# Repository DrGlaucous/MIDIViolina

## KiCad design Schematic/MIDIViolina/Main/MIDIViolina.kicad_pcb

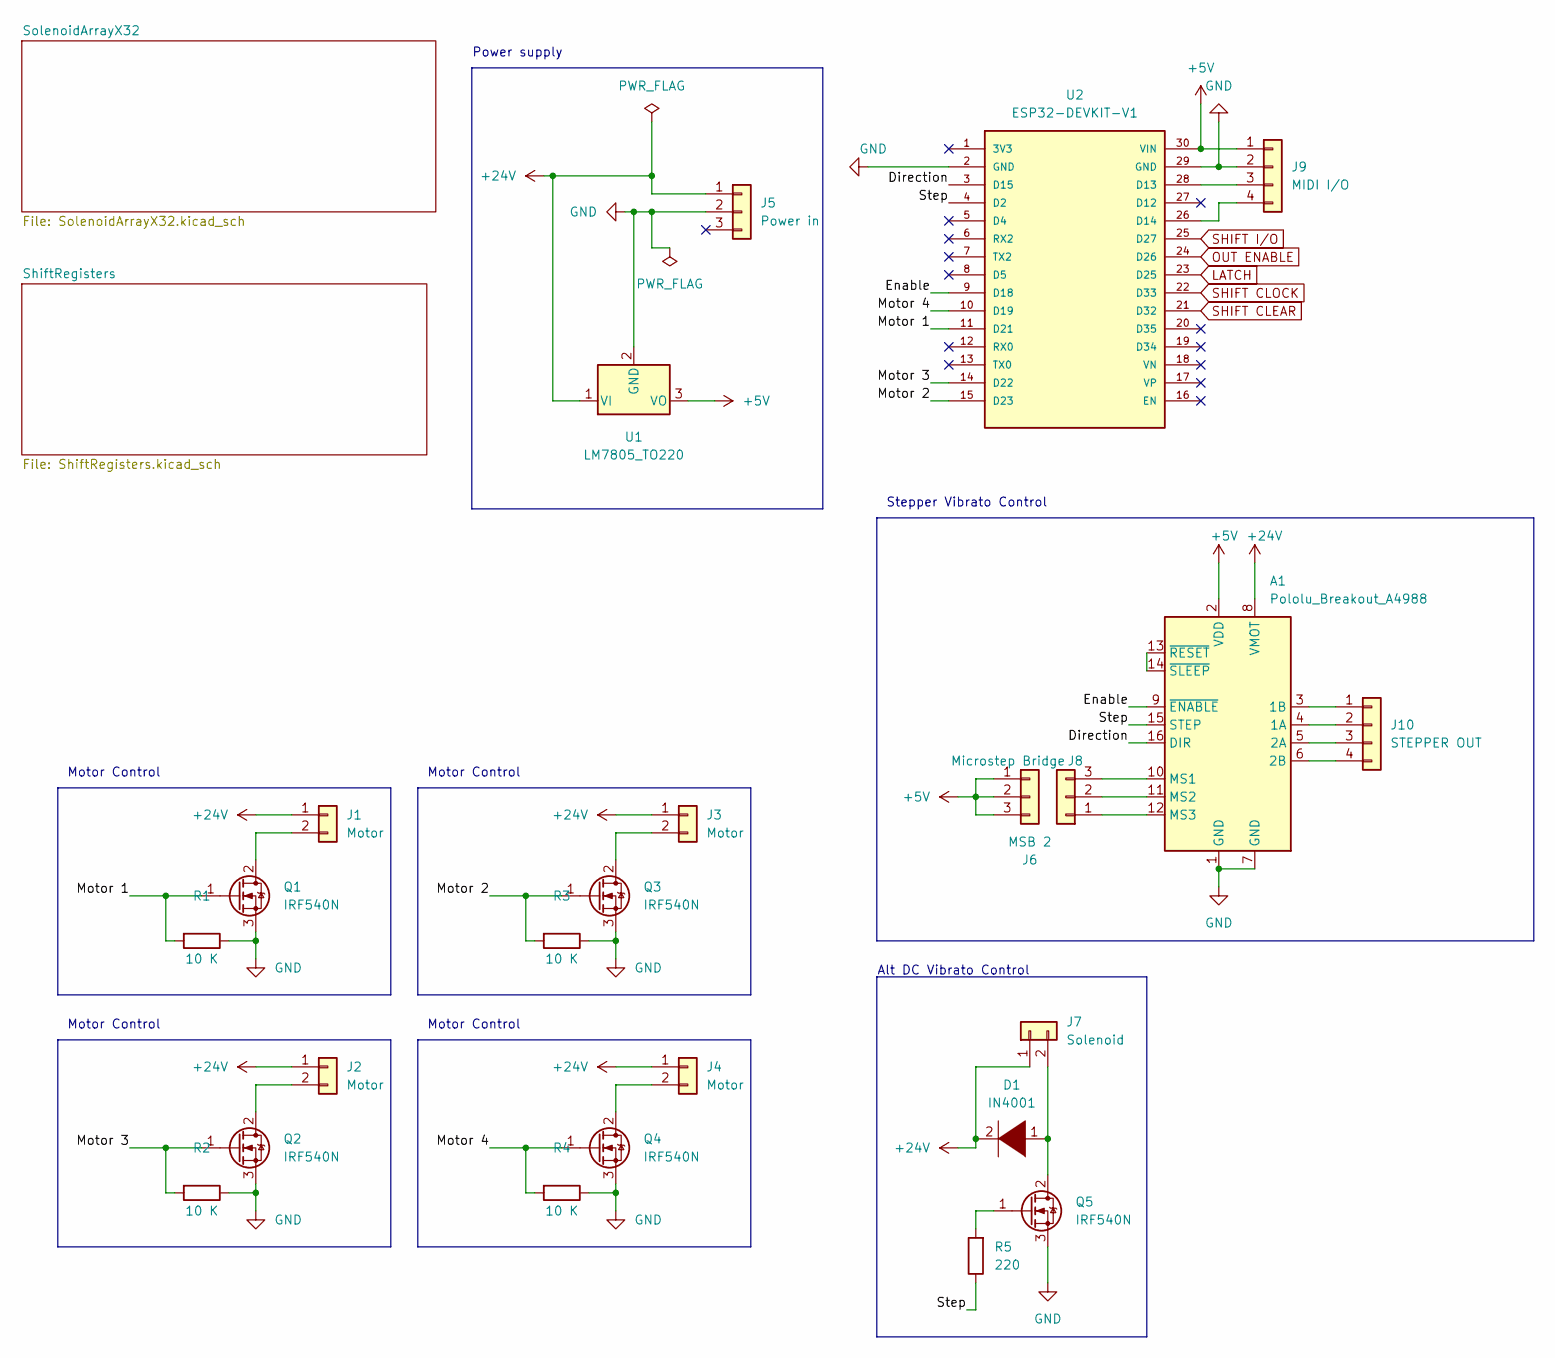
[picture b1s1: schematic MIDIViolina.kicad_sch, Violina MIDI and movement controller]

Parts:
A1: Pololu_Breakout_A4988; Pololu_Breakout-16_15.2x20.3mm
D1: IN4001; D_DO-41_SOD81_P7.62mm_Horizontal
J1, J2, J3, J4: Motor; PinHeader_1x02_P2.54mm_Vertical
J5: Power in; PinHeader_1x03_P2.54mm_Vertical
J6: MSB 2; PinHeader_1x03_P2.54mm_Vertical
J7: Solenoid; PinHeader_1x02_P2.54mm_Vertical
J8: Microstep Bridge; PinHeader_1x03_P2.54mm_Vertical
J9: MIDI I/O; PinHeader_1x04_P2.54mm_Vertical
J10: STEPPER OUT; PinHeader_1x04_P2.54mm_Vertical
Q1, Q2, Q3, Q4, Q5: IRF540N; TO-220-3_Vertical
R1, R2, R3, R4: 10 K; R_Axial_DIN0207_L6.3mm_D2.5mm_P7.62mm_Horizontal
R5: 220; R_Axial_DIN0207_L6.3mm_D2.5mm_P7.62mm_Horizontal
U1: LM7805_TO220; TO-220-3_Vertical
U2: ESP32-DEVKIT-V1; MODULE_ESP32_DEVKIT_V1; PARTREV N/A

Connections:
+5V: A1.2 (VDD), J6.1, J6.2, J6.3, J9.1, U1.3 (VO), U2.30 (VIN); also elsewhere on the board
+24V: A1.8 (VMOT), D1.2 (A), J1.1, J2.1, J3.1, J4.1, J5.1, J7.1, U1.1 (VI); also elsewhere on the board
/Direction: A1.16 (DIR), U2.3 (D15)
/Enable: A1.9 (~ENABLE), U2.9 (D18)
/Motor 1: Q1.1 (G), R1.2, U2.11 (D21)
/Motor 2: Q3.1 (G), R3.2, U2.15 (D23)
/Motor 3: Q2.1 (G), R2.2, U2.14 (D22)
/Motor 4: Q4.1 (G), R4.2, U2.10 (D19)
/Step: A1.15 (STEP), R5.1, U2.4 (D2)
GND: A1.1 (GND), A1.7 (GND), J5.2, J9.2, Q1.3 (S), Q2.3 (S), Q3.3 (S), Q4.3 (S), Q5.3 (S), R1.1, R2.1, R3.1, R4.1, U1.2 (GND), U2.2 (GND), U2.29 (GND); also elsewhere on the board
LATCH: U2.23 (D25); also elsewhere on the board
unnamed: A1.3 (1B), J10.1
unnamed: A1.4 (1A), J10.2
unnamed: A1.5 (2A), J10.3
unnamed: A1.6 (2B), J10.4
unnamed: A1.10 (MS1), J8.3
unnamed: A1.11 (MS2), J8.2
unnamed: A1.12 (MS3), J8.1
unnamed: A1.13 (~RESET), A1.14 (~SLEEP)
unnamed: D1.1 (K), J7.2, Q5.2 (D)
unnamed: J1.2, Q1.2 (D)
unnamed: J2.2, Q2.2 (D)
unnamed: J3.2, Q3.2 (D)
unnamed: J4.2, Q4.2 (D)
unnamed: J9.3, U2.28 (D13)
unnamed: J9.4, U2.26 (D14)
unnamed: Q5.1 (G), R5.2
OUT ENABLE: U2.24 (D26); also elsewhere on the board
SHIFT CLEAR: U2.21 (D32); also elsewhere on the board
SHIFT CLOCK: U2.22 (D33); also elsewhere on the board
SHIFT I/O: U2.25 (D27); also elsewhere on the board

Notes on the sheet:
Motor Control
Alt DC Vibrato Control
Stepper Vibrato Control
Power supply

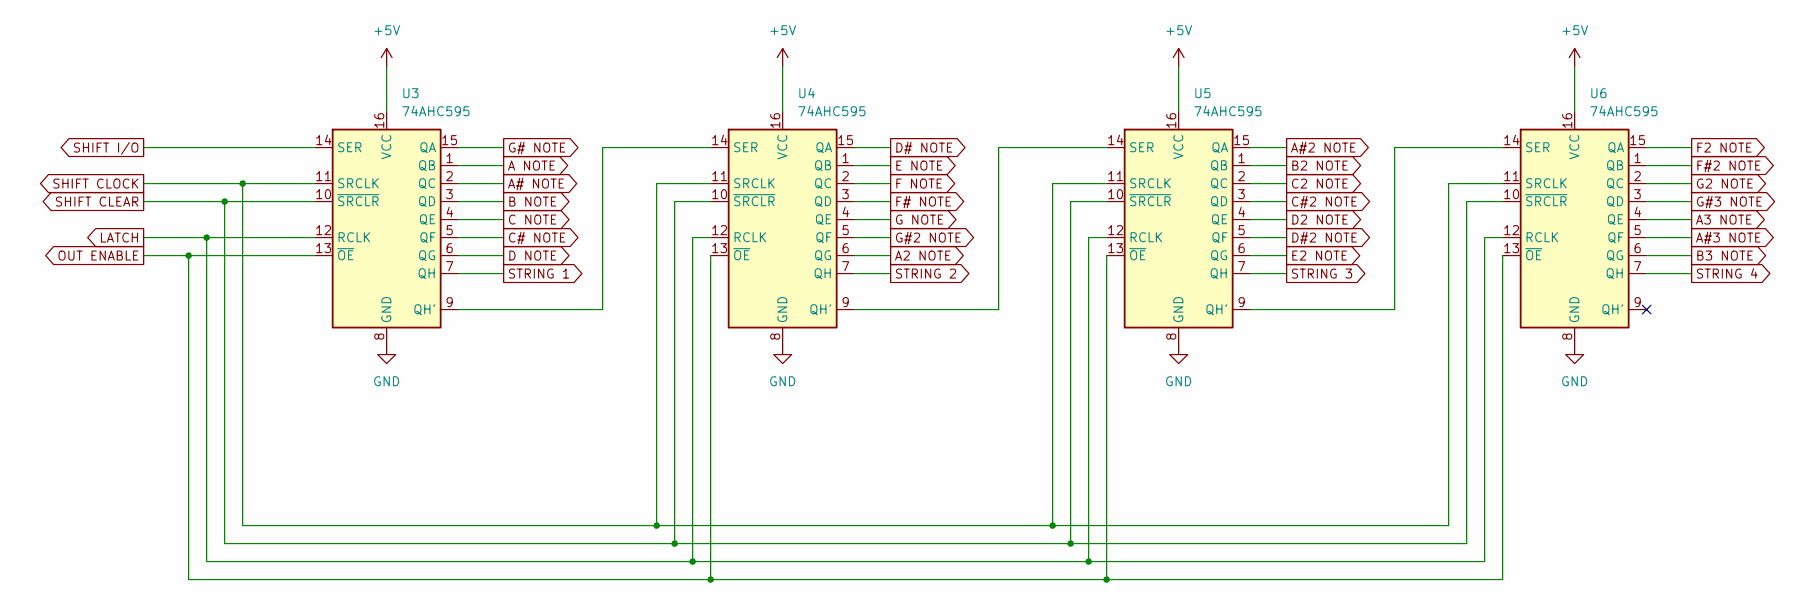
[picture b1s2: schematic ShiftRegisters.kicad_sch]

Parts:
U3, U4, U5, U6: 74AHC595; DIP-16_W7.62mm_LongPads

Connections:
+5V: U3.16 (VCC), U4.16 (VCC), U5.16 (VCC), U6.16 (VCC); also elsewhere on the board
A2 NOTE: U4.6 (QG); also elsewhere on the board
A3 NOTE: U6.4 (QE); also elsewhere on the board
A NOTE: U3.1 (QB); also elsewhere on the board
A#2 NOTE: U5.15 (QA); also elsewhere on the board
A#3 NOTE: U6.5 (QF); also elsewhere on the board
A# NOTE: U3.2 (QC); also elsewhere on the board
B2 NOTE: U5.1 (QB); also elsewhere on the board
B3 NOTE: U6.6 (QG); also elsewhere on the board
B NOTE: U3.3 (QD); also elsewhere on the board
C2 NOTE: U5.2 (QC); also elsewhere on the board
C NOTE: U3.4 (QE); also elsewhere on the board
C#2 NOTE: U5.3 (QD); also elsewhere on the board
C# NOTE: U3.5 (QF); also elsewhere on the board
D2 NOTE: U5.4 (QE); also elsewhere on the board
D NOTE: U3.6 (QG); also elsewhere on the board
D#2 NOTE: U5.5 (QF); also elsewhere on the board
D# NOTE: U4.15 (QA); also elsewhere on the board
E2 NOTE: U5.6 (QG); also elsewhere on the board
E NOTE: U4.1 (QB); also elsewhere on the board
F2 NOTE: U6.15 (QA); also elsewhere on the board
F NOTE: U4.2 (QC); also elsewhere on the board
F#2 NOTE: U6.1 (QB); also elsewhere on the board
F# NOTE: U4.3 (QD); also elsewhere on the board
G2 NOTE: U6.2 (QC); also elsewhere on the board
G NOTE: U4.4 (QE); also elsewhere on the board
G#2 NOTE: U4.5 (QF); also elsewhere on the board
G#3 NOTE: U6.3 (QD); also elsewhere on the board
G# NOTE: U3.15 (QA); also elsewhere on the board
GND: U3.8 (GND), U4.8 (GND), U5.8 (GND), U6.8 (GND); also elsewhere on the board
LATCH: U3.12 (RCLK), U4.12 (RCLK), U5.12 (RCLK), U6.12 (RCLK); also elsewhere on the board
unnamed: U3.9 (QH'), U4.14 (SER)
unnamed: U4.9 (QH'), U5.14 (SER)
unnamed: U5.9 (QH'), U6.14 (SER)
OUT ENABLE: U3.13 (~OE), U4.13 (~OE), U5.13 (~OE), U6.13 (~OE); also elsewhere on the board
SHIFT CLEAR: U3.10 (~SRCLR), U4.10 (~SRCLR), U5.10 (~SRCLR), U6.10 (~SRCLR); also elsewhere on the board
SHIFT CLOCK: U3.11 (SRCLK), U4.11 (SRCLK), U5.11 (SRCLK), U6.11 (SRCLK); also elsewhere on the board
SHIFT I/O: U3.14 (SER); also elsewhere on the board
STRING 1: U3.7 (QH); also elsewhere on the board
STRING 2: U4.7 (QH); also elsewhere on the board
STRING 3: U5.7 (QH); also elsewhere on the board
STRING 4: U6.7 (QH); also elsewhere on the board

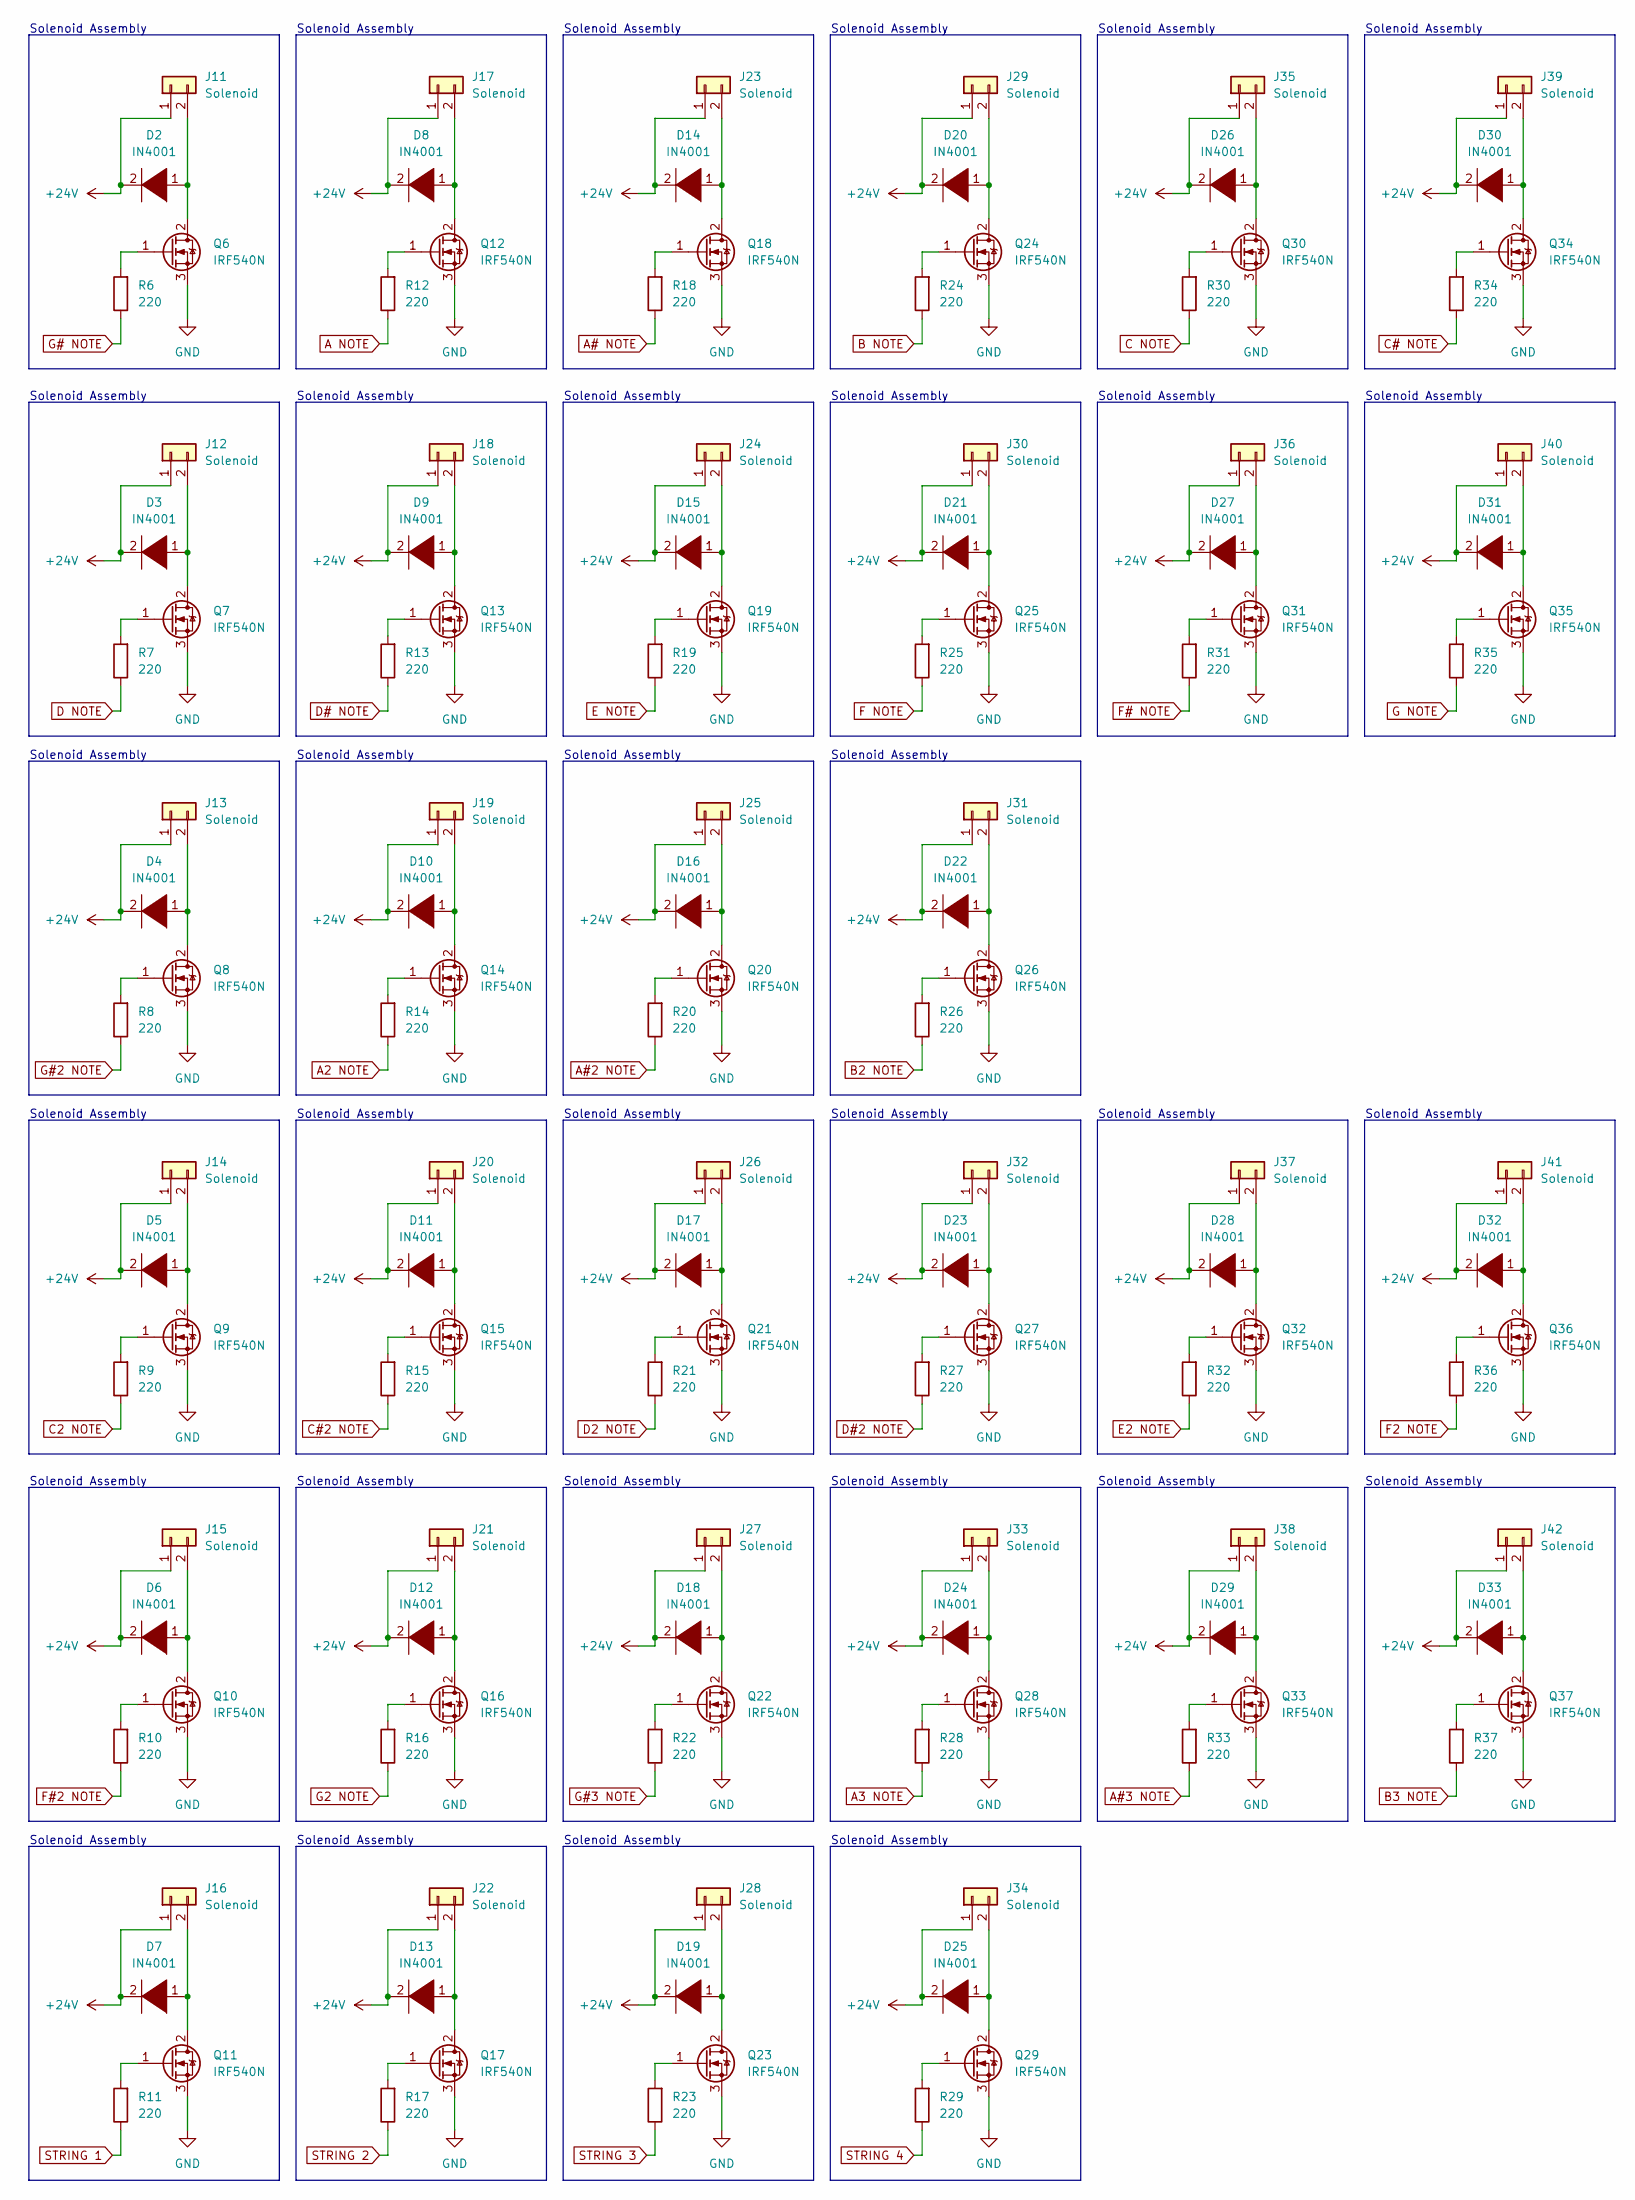
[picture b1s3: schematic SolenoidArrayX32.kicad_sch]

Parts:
D2, D3, D4, D5, D6, D7, D8, D9, D10, D11, D12, D13, D14, D15, D16, D17, D18, D19, D20, D21, D22, D23, D24, D25, D26, D27, D28, D29, D30, D31, D32, D33: IN4001; D_DO-41_SOD81_P7.62mm_Horizontal
J11, J12, J13, J14, J15, J16, J17, J18, J19, J20, J21, J22, J23, J24, J25, J26, J27, J28, J29, J30, J31, J32, J33, J34, J35, J36, J37, J38, J39, J40, J41, J42: Solenoid; PinHeader_1x02_P2.54mm_Vertical
Q6, Q7, Q8, Q9, Q10, Q11, Q12, Q13, Q14, Q15, Q16, Q17, Q18, Q19, Q20, Q21, Q22, Q23, Q24, Q25, Q26, Q27, Q28, Q29, Q30, Q31, Q32, Q33, Q34, Q35, Q36, Q37: IRF540N; TO-220-3_Vertical
R6, R7, R8, R9, R10, R11, R12, R13, R14, R15, R16, R17, R18, R19, R20, R21, R22, R23, R24, R25, R26, R27, R28, R29, R30, R31, R32, R33, R34, R35, R36, R37: 220; R_Axial_DIN0207_L6.3mm_D2.5mm_P7.62mm_Horizontal

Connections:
+24V: D2.2 (A), D3.2 (A), D4.2 (A), D5.2 (A), D6.2 (A), D7.2 (A), D8.2 (A), D9.2 (A), D10.2 (A), D11.2 (A), D12.2 (A), D13.2 (A), D14.2 (A), D15.2 (A), D16.2 (A), D17.2 (A), D18.2 (A), D19.2 (A), D20.2 (A), D21.2 (A), D22.2 (A), D23.2 (A), D24.2 (A), D25.2 (A), D26.2 (A), D27.2 (A), D28.2 (A), D29.2 (A), D30.2 (A), D31.2 (A), D32.2 (A), D33.2 (A), J11.1, J12.1, J13.1, J14.1, J15.1, J16.1, J17.1, J18.1, J19.1, J20.1, J21.1, J22.1, J23.1, J24.1, J25.1, J26.1, J27.1, J28.1, J29.1, J30.1, J31.1, J32.1, J33.1, J34.1, J35.1, J36.1, J37.1, J38.1, J39.1, J40.1, J41.1, J42.1; also elsewhere on the board
A2 NOTE: R14.1; also elsewhere on the board
A3 NOTE: R28.1; also elsewhere on the board
A NOTE: R12.1; also elsewhere on the board
A#2 NOTE: R20.1; also elsewhere on the board
A#3 NOTE: R33.1; also elsewhere on the board
A# NOTE: R18.1; also elsewhere on the board
B2 NOTE: R26.1; also elsewhere on the board
B3 NOTE: R37.1; also elsewhere on the board
B NOTE: R24.1; also elsewhere on the board
C2 NOTE: R9.1; also elsewhere on the board
C NOTE: R30.1; also elsewhere on the board
C#2 NOTE: R15.1; also elsewhere on the board
C# NOTE: R34.1; also elsewhere on the board
D2 NOTE: R21.1; also elsewhere on the board
D NOTE: R7.1; also elsewhere on the board
D#2 NOTE: R27.1; also elsewhere on the board
D# NOTE: R13.1; also elsewhere on the board
E2 NOTE: R32.1; also elsewhere on the board
E NOTE: R19.1; also elsewhere on the board
F2 NOTE: R36.1; also elsewhere on the board
F NOTE: R25.1; also elsewhere on the board
F#2 NOTE: R10.1; also elsewhere on the board
F# NOTE: R31.1; also elsewhere on the board
G2 NOTE: R16.1; also elsewhere on the board
G NOTE: R35.1; also elsewhere on the board
G#2 NOTE: R8.1; also elsewhere on the board
G#3 NOTE: R22.1; also elsewhere on the board
G# NOTE: R6.1; also elsewhere on the board
GND: Q6.3 (S), Q7.3 (S), Q8.3 (S), Q9.3 (S), Q10.3 (S), Q11.3 (S), Q12.3 (S), Q13.3 (S), Q14.3 (S), Q15.3 (S), Q16.3 (S), Q17.3 (S), Q18.3 (S), Q19.3 (S), Q20.3 (S), Q21.3 (S), Q22.3 (S), Q23.3 (S), Q24.3 (S), Q25.3 (S), Q26.3 (S), Q27.3 (S), Q28.3 (S), Q29.3 (S), Q30.3 (S), Q31.3 (S), Q32.3 (S), Q33.3 (S), Q34.3 (S), Q35.3 (S), Q36.3 (S), Q37.3 (S); also elsewhere on the board
unnamed: D2.1 (K), J11.2, Q6.2 (D)
unnamed: D3.1 (K), J12.2, Q7.2 (D)
unnamed: D4.1 (K), J13.2, Q8.2 (D)
unnamed: D5.1 (K), J14.2, Q9.2 (D)
unnamed: D6.1 (K), J15.2, Q10.2 (D)
unnamed: D7.1 (K), J16.2, Q11.2 (D)
unnamed: D8.1 (K), J17.2, Q12.2 (D)
unnamed: D9.1 (K), J18.2, Q13.2 (D)
unnamed: D10.1 (K), J19.2, Q14.2 (D)
unnamed: D11.1 (K), J20.2, Q15.2 (D)
unnamed: D12.1 (K), J21.2, Q16.2 (D)
unnamed: D13.1 (K), J22.2, Q17.2 (D)
unnamed: D14.1 (K), J23.2, Q18.2 (D)
unnamed: D15.1 (K), J24.2, Q19.2 (D)
unnamed: D16.1 (K), J25.2, Q20.2 (D)
unnamed: D17.1 (K), J26.2, Q21.2 (D)
unnamed: D18.1 (K), J27.2, Q22.2 (D)
unnamed: D19.1 (K), J28.2, Q23.2 (D)
unnamed: D20.1 (K), J29.2, Q24.2 (D)
unnamed: D21.1 (K), J30.2, Q25.2 (D)
unnamed: D22.1 (K), J31.2, Q26.2 (D)
unnamed: D23.1 (K), J32.2, Q27.2 (D)
unnamed: D24.1 (K), J33.2, Q28.2 (D)
unnamed: D25.1 (K), J34.2, Q29.2 (D)
unnamed: D26.1 (K), J35.2, Q30.2 (D)
unnamed: D27.1 (K), J36.2, Q31.2 (D)
unnamed: D28.1 (K), J37.2, Q32.2 (D)
unnamed: D29.1 (K), J38.2, Q33.2 (D)
unnamed: D30.1 (K), J39.2, Q34.2 (D)
unnamed: D31.1 (K), J40.2, Q35.2 (D)
unnamed: D32.1 (K), J41.2, Q36.2 (D)
unnamed: D33.1 (K), J42.2, Q37.2 (D)
unnamed: Q6.1 (G), R6.2
unnamed: Q7.1 (G), R7.2
unnamed: Q8.1 (G), R8.2
unnamed: Q9.1 (G), R9.2
unnamed: Q10.1 (G), R10.2
unnamed: Q11.1 (G), R11.2
unnamed: Q12.1 (G), R12.2
unnamed: Q13.1 (G), R13.2
unnamed: Q14.1 (G), R14.2
unnamed: Q15.1 (G), R15.2
unnamed: Q16.1 (G), R16.2
unnamed: Q17.1 (G), R17.2
unnamed: Q18.1 (G), R18.2
unnamed: Q19.1 (G), R19.2
unnamed: Q20.1 (G), R20.2
unnamed: Q21.1 (G), R21.2
unnamed: Q22.1 (G), R22.2
unnamed: Q23.1 (G), R23.2
unnamed: Q24.1 (G), R24.2
unnamed: Q25.1 (G), R25.2
unnamed: Q26.1 (G), R26.2
unnamed: Q27.1 (G), R27.2
unnamed: Q28.1 (G), R28.2
unnamed: Q29.1 (G), R29.2
unnamed: Q30.1 (G), R30.2
unnamed: Q31.1 (G), R31.2
unnamed: Q32.1 (G), R32.2
unnamed: Q33.1 (G), R33.2
unnamed: Q34.1 (G), R34.2
unnamed: Q35.1 (G), R35.2
unnamed: Q36.1 (G), R36.2
unnamed: Q37.1 (G), R37.2
STRING 1: R11.1; also elsewhere on the board
STRING 2: R17.1; also elsewhere on the board
STRING 3: R23.1; also elsewhere on the board
STRING 4: R29.1; also elsewhere on the board

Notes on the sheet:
Solenoid Assembly

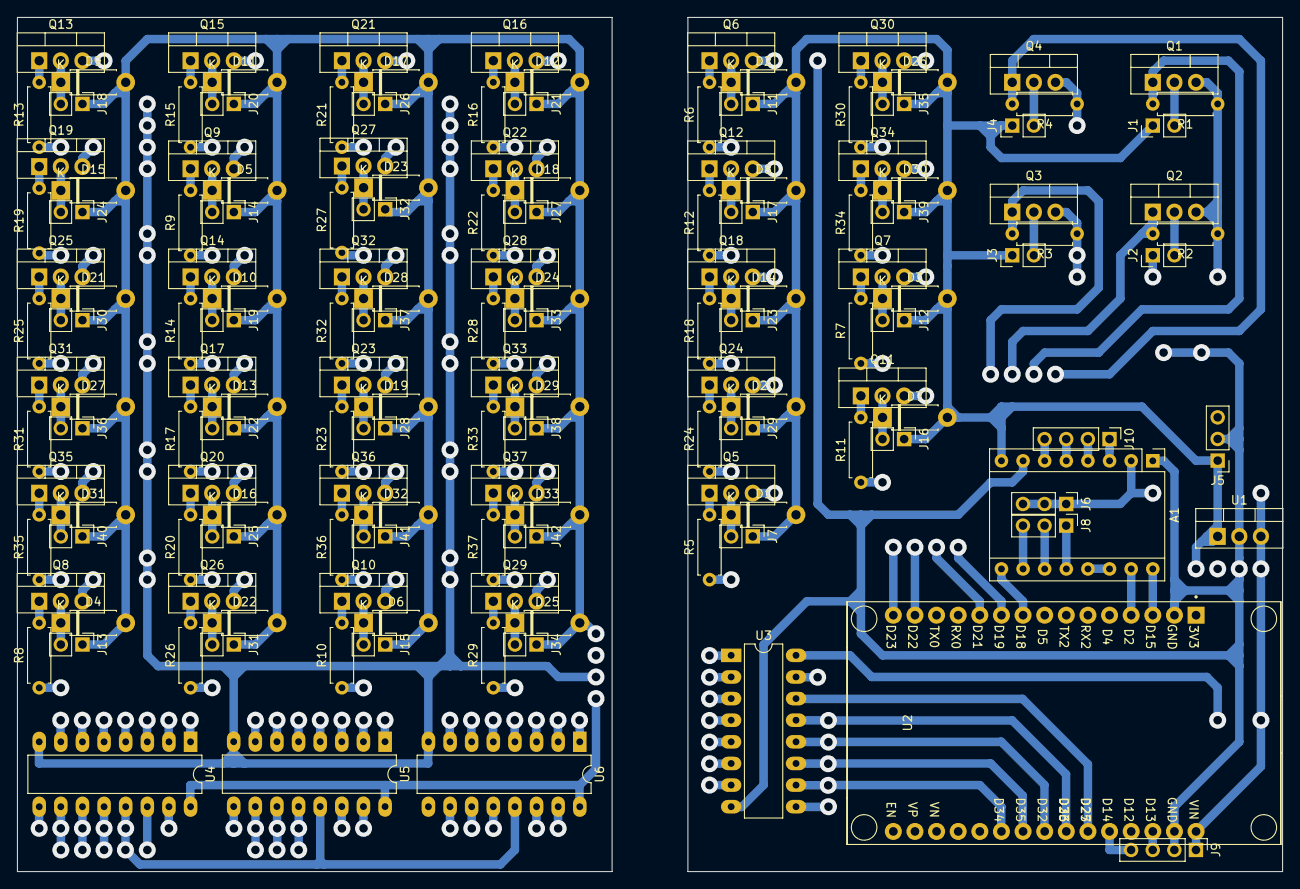
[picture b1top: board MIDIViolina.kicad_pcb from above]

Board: 2 copper layers, 148.6 x 100.3 mm, 156 parts (0 on the bottom side), 130 nets.

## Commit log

2022-08-22 initial commit
    every project starts somewhere. this one starts here.
2022-09-21 moved some files
    made it smaller
2022-10-11 CAD
    PCBs and physical structure
2022-11-12 CAD work done
    started prototyping in sketchup (much faster)
2022-11-13 Cad work done (in Sketchup this time)
    I was able to do in a day with sketchup what solidworks took me a week
2022-11-13 update a few more files
    x2 work on different machines
2022-11-14 CAD work, optimizing for printing
2022-11-15 CAD updates
2022-11-23 many cad updates
2022-11-29 model changes
2022-12-05 throwing CAD files
2022-12-05 CNC Toolpaths and PCB updates
2022-12-07 CAM and PCB manufacture
    Generated CAM instructions for CNC mill
2022-12-17 updated CAD
2022-12-18 update PCB schematics
2023-01-10 started on firmware
2023-01-10 started building firmware
2023-01-10 program updates
2023-01-23 some schematic updates
    found a pinout error where I had them hooked up to "input only" pins. Corrected this issue.
2023-01-23 firmware R&D
2023-01-23 recover autosave with updated violin clamps
2023-02-01 changed from MIDI.h to control surface library
    the MIDI library was failing to catch all midi events
2023-02-01 fix pin routing problems
    added extra thru-vias and corrected pinouts
2023-02-06 update PCB and added rosen wheel
